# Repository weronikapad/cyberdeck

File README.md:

# Raspberry pi pico cyberek

## Function:
It's a retro inspired minicomputer, and hopefully a debugger, built on a raspberry pi pico, rn the files only present a mother board but i will be adding a keybord, screen, sd card, and i LiPo battery

## Sepecifics:
-Raspbery pi pico (Raspberry_Pi_Pico)
-USB-C port (USB_C_Receptable_USB.2.0_14P)
-Power manager (TP4057)
-Battery connector (Conn_01x02)
-screen connector (J2 Conn_01x08)
-column connector (J5 Conn_01x08)
-keyboard connector (Conn_01x04)

## Files
-/gerber/ PCB munfactoring files
-/cyberek_schematic.kicad.sch KiCad schematic
-/cyberdeck_pcb.kicad_pcb KiCad PCB layout file
-/cyberdeck_pcb.kicad_pro General PCB KiCad file

## To order:
upload gerebr.zip to https://jlcpcb.com/

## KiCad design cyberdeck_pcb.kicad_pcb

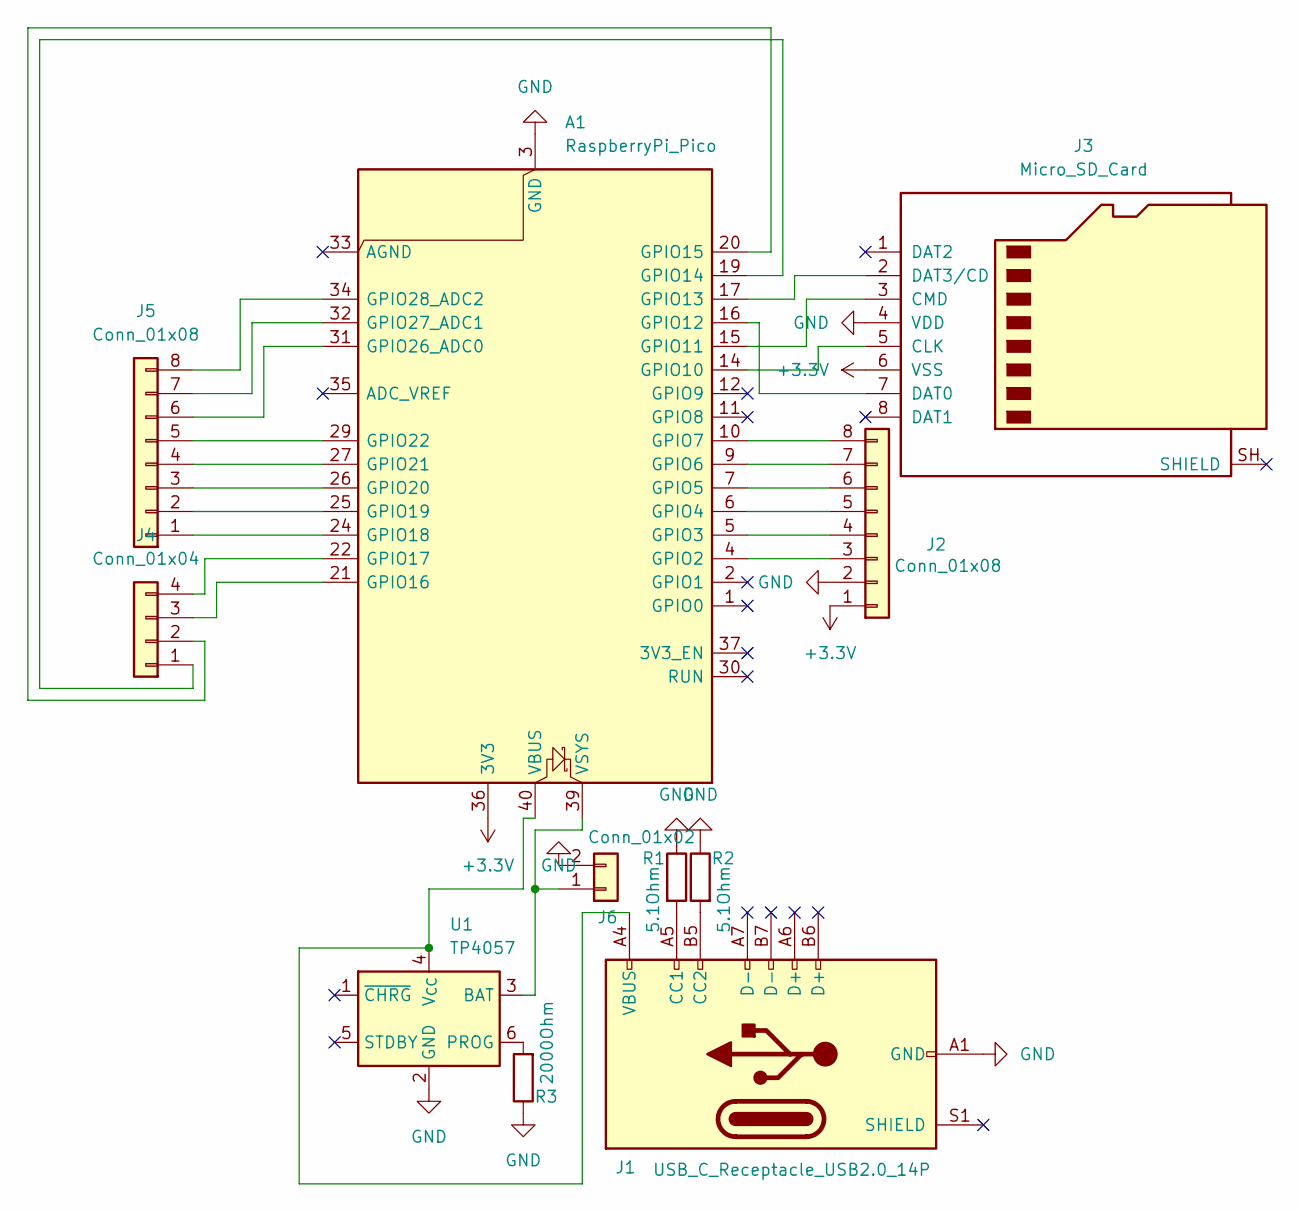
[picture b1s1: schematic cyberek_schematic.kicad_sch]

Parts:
A1: RaspberryPi_Pico; RaspberryPi_Pico_Common_Unspecified
J1: USB_C_Receptacle_USB2.0_14P; USB_C_Receptacle_GCT_USB4110
J2, J5: Conn_01x08; PinHeader_1x08_P2.54mm_Vertical
J3: Micro_SD_Card; microSD_HC_Molex_47219-2001
J4: Conn_01x04; PinHeader_1x04_P2.54mm_Vertical
J6: Conn_01x02; PinSocket_1x02_P2.54mm_Vertical
R1, R2: 5.1Ohm; R_0805_2012Metric
R3: 2000Ohm; R_0815_2038Metric
U1: TP4057; TSOT-23-6

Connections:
+3.3V: A1.36 (3V3), J2.1, J3.6 (VSS)
GND: A1.3 (GND), A1.8 (GND), A1.13 (GND), A1.18 (GND), A1.23 (GND), A1.28 (GND), A1.38 (GND), J1.A1 (GND), J1.A12 (GND), J1.B1 (GND), J1.B12 (GND), J2.2, J3.4 (VDD), J6.2, R1.1, R2.1, R3.1, U1.2 (GND)
unnamed: A1.4 (GPIO2), J2.3
unnamed: A1.5 (GPIO3), J2.4
unnamed: A1.6 (GPIO4), J2.5
unnamed: A1.7 (GPIO5), J2.6
unnamed: A1.9 (GPIO6), J2.7
unnamed: A1.10 (GPIO7), J2.8
unnamed: A1.14 (GPIO10), J3.5 (CLK)
unnamed: A1.15 (GPIO11), J3.3 (CMD)
unnamed: A1.16 (GPIO12), J3.7 (DAT0)
unnamed: A1.17 (GPIO13), J3.2 (DAT3/CD)
unnamed: A1.19 (GPIO14), J4.1
unnamed: A1.20 (GPIO15), J4.2
unnamed: A1.21 (GPIO16), J4.3
unnamed: A1.22 (GPIO17), J4.4
unnamed: A1.24 (GPIO18), J5.1
unnamed: A1.25 (GPIO19), J5.2
unnamed: A1.26 (GPIO20), J5.3
unnamed: A1.27 (GPIO21), J5.4
unnamed: A1.29 (GPIO22), J5.5
unnamed: A1.31 (GPIO26_ADC0), J5.6
unnamed: A1.32 (GPIO27_ADC1), J5.7
unnamed: A1.34 (GPIO28_ADC2), J5.8
unnamed: A1.40 (VBUS), J1.A4 (VBUS), J1.A9 (VBUS), J1.B4 (VBUS), J1.B9 (VBUS), U1.4 (V_{CC})
unnamed: A1.39 (VSYS), J6.1, U1.3 (BAT)
unnamed: J1.A5 (CC1), R1.2
unnamed: J1.B5 (CC2), R2.2
unnamed: R3.2, U1.6 (PROG)

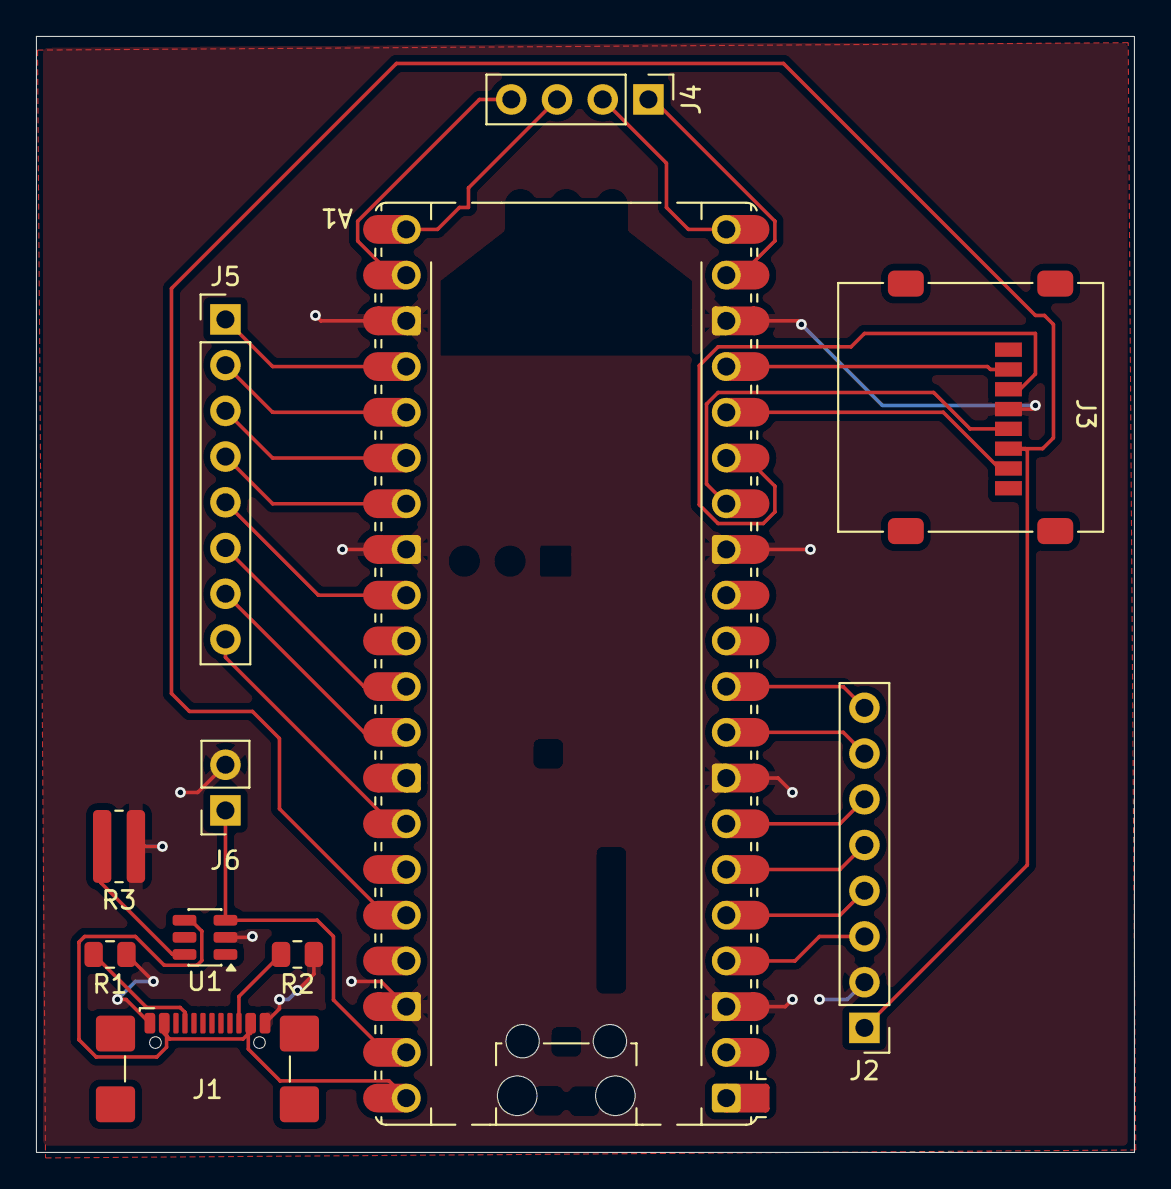
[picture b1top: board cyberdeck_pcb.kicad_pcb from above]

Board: 2 copper layers, 61.0 x 62.0 mm, 11 parts (0 on the bottom side), 29 nets.

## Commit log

2026-05-02 README
2026-05-02 tittle fix
